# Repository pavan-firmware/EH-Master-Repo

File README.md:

# EH Home — Production Smart-Home Platform Monorepo

Welcome to the **EH Home** ecosystem repository. EH Home is an enterprise-grade, edge-autonomous, local-first smart-home platform supporting multi-gang smart switches (1X/2X/3X/4X), sockets, fan regulators, CCT/dimmable lighting, deterministic energy monitoring, on-chip FreeRTOS automation, and multi-protocol hardware abstraction (Wi-Fi, BLE, Thread, Matter).

---

## 1. Monorepo Architecture Overview

The workspace is organized as a unified monorepo engineered for strict contract safety, zero-downtime offline execution, and metadata-driven UI:

```
SMART_HOME_V1/
├── apps/
│   ├── api/                     # High-performance Fastify REST API & SSE Realtime Engine
│   └── desktop/                 # Tauri v2 + Rust + React Desktop Suite (Bench Provisioner, TSPL, Packing)
├── assets/                      # Brand, visual assets & product iconography
├── backend/                     # Node.js backend services, migrations, repositories & workers
│   ├── migrations/              # 37 symmetric UP/DOWN PostgreSQL migrations & seed data
│   ├── src/                     # Repositories, domain services, and REST/SSE API routers
│   └── tests/                   # Monorepo database integration, hardening & lifecycle test suites
├── docs/                        # Complete technical architecture, ADRs, runbooks & phase reports
│   ├── adr/                     # Architectural Decision Records (ADR-000 through ADR-004)
│   ├── architecture/            # Architecture specifications, Parts 00–17 & business guides
│   ├── contracts/               # Protocol contracts & deterministic energy specifications
│   ├── manufacturing/           # Factory bench provisioning & thermal label printing guides
│   └── reconciliation/          # Technical reconciliation audits & feature completion registers
├── firmware/                    # Production ESP32 embedded firmware
│   ├── platforms/esp32/         # FreeRTOS firmware (Edge Routine Engine, UDP Discovery, mTLS MQTT, OTA)
│   └── legacy-v1/               # Preserved legacy node/hub reference implementation
├── packages/
│   ├── contracts/               # Canonical Draft-07 JSON Schemas, TypeScript contracts & validators
│   └── db-schema/               # Drizzle ORM relational models & database definitions
├── product-definitions/         # Metadata-driven product catalog definitions (SKUs & hardware profiles)
├── smart_home_application_v1/   # Production Flutter mobile application (iOS, Android, Web)
│   ├── lib/                     # Stale-while-revalidate UI, capability engine, theme tokens, controllers
│   └── test/                    # Full unit, widget, lifecycle & capability regression test suites
├── tools/
│   ├── database/                # Backup, restore & replication utilities
│   ├── device-simulator/        # Contract-compliant device hardware simulator
│   ├── hardware-test-harness/   # Python hardware loopback and ESP32 lifecycle runner
│   └── manufacturing/           # Factory flasher, PKI manager & TSPL label generators
├── scripts/
│   └── validate-repo.js         # Master CI pre-push validation suite (80 comprehensive test suites)
├── .env.example                 # Local development configuration template
└── docker-compose.yml           # Local infrastructure stack (PostgreSQL, Redis, EMQX 5.8.0, MinIO)
```

---

## 2. Platform Architecture Phases (Phases 1 — 50)

| Phase Range | Subsystems Covered | Key Capabilities Implemented | Status |
|:---|:---|:---|:---:|
| **Phases 1–4** | Contracts, Persistence, Catalog & Domain | 19 canonical Draft-07 JSON schemas, PostgreSQL persistence, catalog discovery, home/floor/room/device domain entities. | ✅ Complete |
| **Phases 5–7** | Onboarding, Transports & Realtime | EH-PROV/1 BLE commissioning (AES-256-GCM, HKDF), EMQX 5.8.0 mTLS transport with per-device ACLs, RS256 JWT auth, realtime SSE event bus. | ✅ Complete |
| **Phases 8–11** | PKI, Automations & Fleet Reliability | Manufacturing root PKI, signed dual-slot OTA rollback, FreeRTOS edge routine engine, hardware watchdog & auto-healing. | ✅ Complete |
| **Phases 12–18** | Security, Fleet Rollout & Cloud Sync | Multi-tenant RBAC, remote backup storage, staggered OTA fleet deployments, disaster recovery snapshotting. | ✅ Complete |
| **Phases 19–25** | Energy, Tariffs & Decision Intelligence | Fixed-point energy telemetry (`BL0942`), ToU dynamic tariffs, energy optimization engine, occupancy presence inference. | ✅ Complete |
| **Phases 26–30** | Edge Control, Matter & User Alerts | Multi-protocol connectivity (Wi-Fi/BLE/Thread/Matter), local-first LAN UDP control (`<15ms`), smart notification de-duplication. | ✅ Complete |
| **Phases 31–36** | Security Hardening & Runtime Auth | Device trust center, cryptographic attestation, role-gated admin console, hardcoded breaker elimination, Flutter lifecycle convergence. | ✅ Complete |
| **Phases 37–46** | Database Scale, Manufacturing & Acceptance | 37 symmetric database migrations, MinIO S3 remote storage, bench flasher, automated thermal label printing, dual-scan packing station. | ✅ Complete |
| **Phases 47–48** | ESP32 Hardware Integration & RBAC | Physical ESP32 target verification, non-EM/EM switch variants, home ownership & membership RBAC (`OWNER`, `ADMIN`, `MEMBER`, `GUEST`). | ✅ Complete |
| **Phase 49** | Edge Routine Engine & Zero-Touch LAN | FreeRTOS on-chip timer routine engine, zero-touch UDP LAN switchover, dual-scan factory packing station, Windows PDF printing subsystem. | ✅ Complete |
| **Phase 50** | Resilience, Dark Theme & Master Flows | Offline stale-while-revalidate, dark-theme contrast tokens, routine notification filtering, truthful MQTT standby reporting, home owner admin access control. | ✅ Complete |

---

## 3. Core Architectural Principles

1. **Hardware is the Authority:** Physical switch toggles execute immediately at the hardware relay. Backend derives `actualState` from `reportedState`; conflicting in-flight cloud commands converge to `OVERRIDDEN`.
2. **Local-First & Edge-Autonomous:** Smart switches and sockets store routines in on-chip non-volatile storage (NVS). Routines execute via FreeRTOS hardware timers even if Wi-Fi or cloud connections are down.
3. **Zero-Touch LAN Control:** When the mobile app is on the local Wi-Fi network, commands travel directly over private LAN HTTP/UDP with `<15ms` latency. When outside, the app automatically transitions to TLS MQTT via the cloud backend.
4. **Role-Based Home Access Control (RBAC):**
   - **`OWNER`**: Full administrative authority over home, disaster recovery snapshots, device trust certificates, members, and billing.
   - **`ADMIN`**: Household management, rooms, device pairing, and routine scheduling.
   - **`MEMBER` / `GUEST`**: Day-to-day actuator controls and scene triggering with strict exclusion from system-level administrative pages.
5. **Deterministic Energy Telemetry:** All electrical measurements are fixed-point unsigned integers on wire (`v_mv`, `i_ma`, `p_mw`, `e_tot_wh`, `pf_x1000`) ensuring exact financial and consumption precision.
6. **Stale-While-Revalidate UX:** Settings, home details, dashboards, and routines display instantly from persistent local storage during offline cold starts or screenshot events, refreshing quietly in the background without blanking screens.

---

## 4. Local Development & Verification

### Prerequisites
- **Node.js**: `v20.x` or later (pnpm recommended)
- **Flutter SDK**: `3.12.x` or later (Dart 3.x)
- **Docker & Docker Compose** (for PostgreSQL, Redis, EMQX 5.8.0, MinIO)
- **Rust Toolchain**: `1.75+` (for Desktop Tauri suite)

### Quick Start
1. Copy the environment configuration:
   ```bash
   cp .env.example .env
   ```
2. Start local infrastructure services:
   ```bash
   docker compose up -d
   ```
3. Run the full pre-push validation suite (all 80 suites):
   ```bash
   node scripts/validate-repo.js
   ```
4. Run Flutter mobile application analyzer and tests:
   ```bash
   cd smart_home_application_v1
   flutter analyze
   flutter test
   ```

---

## 5. Master Validation Suite Overview

The monorepo includes an automated pre-push gate (`scripts/validate-repo.js`) executing **80 comprehensive test suites** covering all platform layers:

```
===============================================================
       EH HOME MONOREPO — PRE-PUSH FULL VALIDATION SUITE       
===============================================================
  [PASS]  1. Canonical Contract Hardening Tests
  [PASS]  2. Product Catalog Definition Validation
  [PASS]  3. Device Simulator Contract Compliance
  [PASS]  4. SQL Migration Lifecycle & Capability Sync (37 Migrations)
  [PASS]  5. Backend DB & Repository Integration Tests
  [PASS]  6. Backend Hardening Test Suite (Auth, State, Idempotency)
  [PASS]  7. Product Catalog Service & API Router Tests
  [PASS]  8. Phase 4 Backend Domain Model & Service Tests
  [PASS]  9. Phase 5 Backend Secure Onboarding & Claiming Tests
  [PASS] 10. Phase 6 MQTT Transport Unit/Mock Tests
  [PASS] 11. Phase 6 Low-Level MQTT Protocol Harness Tests
  [PASS] 12. Phase 6 Real EMQX 5.8.0 Integration Tests
  [PASS] 13. Phase 7A Backend Auth & Authorization Tests
  [PASS] 14. Phase 7B Realtime SSE & Worker Integration Tests
  [PASS] 15. Flutter Analyzer (smart_home_application_v1)
  [PASS] 16. Flutter Test Suite (smart_home_application_v1)
  ...
  [PASS] 72. Part 15 Desktop E2E & Cross-Layer Integration Tests
  [PASS] 73. Part 16 Storage Contracts Hardening
  [PASS] 74. Part 16 S3-Compatible Storage Provider Tests
  [PASS] 75. Part 16 Database Backup, Restore & Recovery Tests
  [PASS] 76. Part 16 Storage & Backup HTTP API Route Tests
===============================================================
  80 SUITES ATTEMPTED: 80 PASSED, 0 SKIPPED, 0 FAILED.
  ALL ATTEMPTED TEST SUITES COMPLETED WITHOUT FAILURE.
===============================================================
```

---

## 6. Security, Governance & Compliance

- **Zero Committed Secrets:** All certificates (`.pem`, `.crt`), keys (`.key`), and tokens are injected via environment variables or generated ephemerally during manufacturing bench flows.
- **Strict Lint & Contract Guard:** Any modification to schemas in `packages/contracts/` must pass Draft-07 validation and maintain bidirectional compatibility across mobile, backend, and firmware.
- **Git Housekeeping:** Test assets and scratch images (`prompt_images/`) are explicitly excluded from repository history via `.gitignore`.

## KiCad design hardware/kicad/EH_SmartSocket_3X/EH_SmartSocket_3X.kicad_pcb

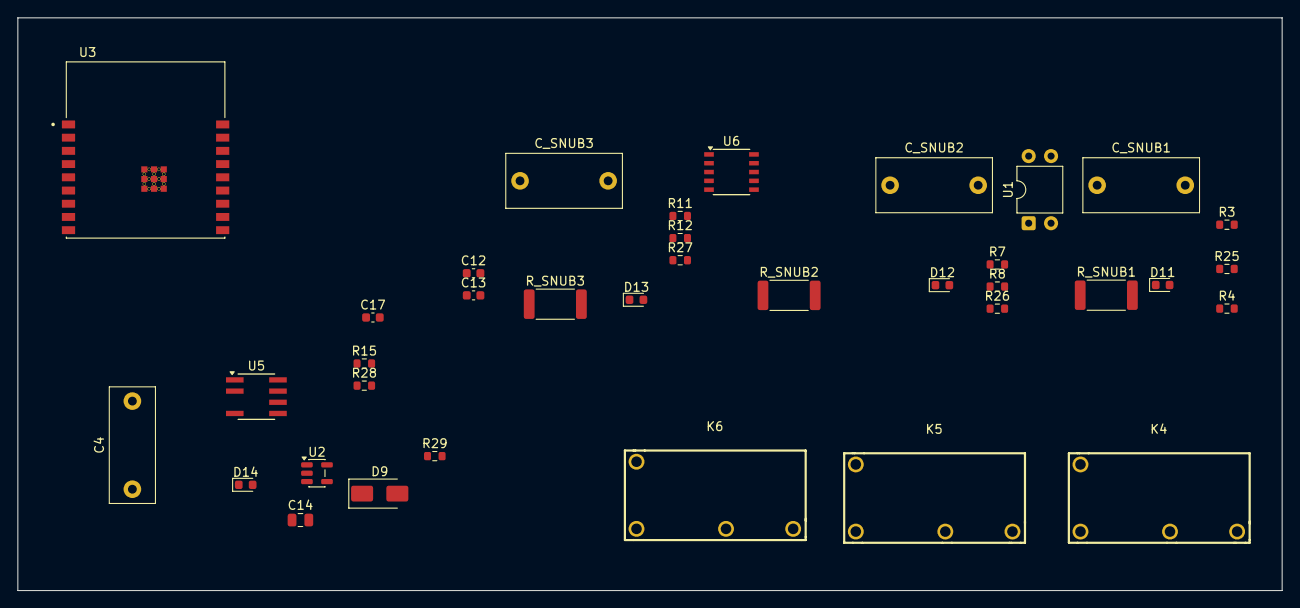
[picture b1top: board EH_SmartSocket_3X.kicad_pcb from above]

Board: 2 copper layers, 143.5 x 65.0 mm, 36 parts (0 on the bottom side), 31 nets, no tracks yet.

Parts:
C4: 0.1uF 275VAC X2; C_Rect_L13.0mm_W5.0mm_P10.00mm_FKS3_FKP3_MKS4
C12: 100nF; C_0603_1608Metric
C13: 1uF|16v; C_0603_1608Metric
C14: 10uF; C_0805_2012Metric
C17: 0.1uF; C_0603_1608Metric
C_SNUB1, C_SNUB2, C_SNUB3: 100nF|630V; C_Rect_L13.0mm_W6.0mm_P10.00mm_FKS3_FKP3_MKS4
D9: STTH1R06U; D_SMA
D11, D12, D13: LED_RL; LED_0603_1608Metric
D14: LED_GREEN; LED_0603_1608Metric
K4, K5, K6: HF33F/005-HS3; RELAYS-TH_HF33F-XX-HS1-XXX
R3, R7, R11, R25, R26, R27: 1K; R_0603_1608Metric
R4, R8, R12, R15, R29: 10K; R_0603_1608Metric
R28: 1.5K; R_0603_1608Metric
R_SNUB1, R_SNUB2, R_SNUB3: 100; R_2512_6332Metric
U1: PC817; DIP-4_W7.62mm
U2: AP2112K-3.3; SOT-23-5
U3: ESP32-C3-WROOM-02-N4; MODULE_ESP32-C3-WROOM-02-H4
U5: LNK3206D; PowerIntegrations_SO-8C
U6: SSOP-10_3.9x4.9mm_P1.00mm

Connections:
+3V3: C14.2, C17.1, R15.2, R28.1, R29.1, U2.5 (VOUT), U3.1 (3V3), U6.1 (VDD)
+5V: K4.1, K5.1, K6.1, R25.1, R26.1, R27.1, U1.1, U2.1 (VIN), U2.3 (EN)
/BL_RX: U3.6 (IO7), U6.10 (TX/SDO)
/BOOT_BTN: C12.2, R15.1, U3.8 (IO9)
/EN: C13.1, R29.2, U3.2 (EN)
/LKN_FB: U1.3, U5.2 (FB)
/LNK_BP: U1.4, U5.1 (BP/M)
/RLY_CH1: R3.1, U3.13 (IO18)
/RLY_CH2: R7.1, U3.14 (IO19)
/RLY_CH3: R11.1, U3.10 (IO10)
GND: C12.1, C13.2, C14.1, C17.2, D9.2 (A), D14.1 (K), R4.1, R8.1, R12.1, U2.2 (GND), U3.9 (GND), U3.19 (GND), U3.20 (GND), U3.21 (GND), U3.22 (GND), U3.23 (GND), U3.24 (GND), U3.25 (GND), U3.26 (GND), U3.27 (GND), U3.28 (GND), U3.29 (GND), U3.30 (GND), U3.31 (GND), U3.32 (GND), U3.33 (GND), U3.34 (GND), U3.35 (GND), U3.36 (GND), U3.37 (GND), U3.38 (GND), U3.39 (GND), U6.5 (GND), U6.7 (SEL), U6.8 (SCLK_BPS)
unnamed: C_SNUB1.1, R_SNUB1.2
unnamed: C_SNUB1.2, K4.3
unnamed: C_SNUB2.1, R_SNUB2.2
unnamed: C_SNUB2.2, K5.3
unnamed: C_SNUB3.1, R_SNUB3.2
unnamed: C_SNUB3.2, K6.3
unnamed: D9.1 (K), U5.5 (S), U5.6 (S), U5.7 (S), U5.8 (S)
unnamed: D11.2 (A), R25.2
unnamed: D11.1 (K), K4.6
unnamed: D12.2 (A), R26.2
unnamed: D12.1 (K), K5.6
unnamed: D13.2 (A), R27.2
unnamed: D13.1 (K), K6.6
unnamed: D14.2 (A), R28.2
unnamed: K4.2, R_SNUB1.1
unnamed: K5.2, R_SNUB2.1
unnamed: K6.2, R_SNUB3.1
unnamed: R3.2, R4.2
unnamed: R7.2, R8.2
unnamed: R11.2, R12.2

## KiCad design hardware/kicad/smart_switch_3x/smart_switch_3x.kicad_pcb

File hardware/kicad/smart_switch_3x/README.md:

# EH Home — KiCad 7 / 8 Production Hardware Project

This directory contains the **KiCad Schematic and PCB Design Project** for the **EH Smart Switch (3X / 4X Channel with BL0942 Metering)**.

---

## 1. Project Files

- **`smart_switch_3x.kicad_pro`**: KiCad Project File.
- **`smart_switch_3x.kicad_sch`**: KiCad Schematic Source.
- **`netlist_smart_switch_3x.net`**: Universal Netlist (can be imported into KiCad, EasyEDA, Altium, or OrCAD).

---

## 2. Universal Schematic Netlist & Pin Connections

Below is the complete machine-readable netlist and pin-to-pin wiring map:

### **Subsystem 1: Mains AC Input & Surge Protection**
| Component | Designator | Pin 1 | Pin 2 | Pin 3 / 4 / 5 | Notes |
| :--- | :--- | :--- | :--- | :--- | :--- |
| Screw Terminal (AC IN) | J1 | `MAINS_LIVE` | `MAINS_NEUTRAL` | `EARTH_GND` | 5.08mm pitch, 16A rated |
| Fuse 2A 250V | F1 | `MAINS_LIVE` | `FUSE_OUT` | — | Micro TR5 / Radial |
| Varistor (MOV) 14D561K | MOV1 | `FUSE_OUT` | `MAINS_NEUTRAL` | — | Clamps surges $\ge 350\text{VAC}$ / 560V |
| NTC Thermistor 10D-9 | NTC1 | `FUSE_OUT` | `AC_L_FILTERED` | — | Limits inrush current |
| Safety Cap 0.1µF 275VAC | CX1 | `AC_L_FILTERED` | `MAINS_NEUTRAL` | — | Class-X2 EMI Suppression |
| Isolated SMPS (HLK-PM01) | U2 | Pin 1: `AC_L_FILTERED` | Pin 2: `MAINS_NEUTRAL` | Pin 3: `+5V`, Pin 4: `GND` | 3kV Isolation AC $\to$ 5V DC |

---

### **Subsystem 2: Low-Voltage Power Regulation (5V $\to$ 3.3V)**
| Component | Designator | Pin 1 | Pin 2 | Pin 3 | Pin 4 | Pin 5 |
| :--- | :--- | :--- | :--- | :--- | :--- | :--- |
| LDO Regulator (AP2112K-3.3) | U3 | `+5V` (VIN) | `GND` | `+5V` (EN) | `NC` | `+3V3` (VOUT) |
| Bulk Filter Capacitor | C1 | `+5V` | `GND` | — | — | 470µF 16V Low-ESR |
| LDO Output Capacitor | C2 | `+3V3` | `GND` | — | — | 100µF 10V Tantalum/Alum |
| Decoupling Capacitors | C3, C4 | `+3V3` | `GND` | — | — | 0.1µF 50V X7R (0603) |

---

### **Subsystem 3: Microcontroller (ESP32-C6-WROOM-1-N4)**
| Pin Name | ESP32-C6 Pin | Connected Net | Description / Function |
| :--- | :--- | :--- | :--- |
| `3V3` | Pin 1, 2 | `+3V3` | Main 3.3V Power Rail |
| `GND` | Pin 3, 14, 29 | `GND` | System Digital Ground |
| `EN` / `CHIP_PU` | Pin 4 | `MCU_EN` | 10kΩ pull-up to 3.3V + 1µF cap to GND |
| `GPIO 4` | Pin 5 | `SW_IN_1` | Channel 1 Wall Switch Input (RC Filtered) |
| `GPIO 5` | Pin 6 | `SW_IN_2` | Channel 2 Wall Switch Input (RC Filtered) |
| `GPIO 6` | Pin 7 | `SW_IN_3` | Channel 3 Wall Switch Input (RC Filtered) |
| `GPIO 7` | Pin 8 | `BL0942_TX_OUT` | BL0942 UART1 Data In (4800 baud) |
| `GPIO 8` | Pin 9 | `STATUS_LED_DRIVE` | 1kΩ Resistor $\to$ Blue Status LED $\to$ GND |
| `GPIO 9` | Pin 10 | `BOOT_SW` | Tactile Button to GND (10s Hold = Reset) |
| `GPIO 16` | Pin 17 | `FACTORY_TX` | Factory Programming UART0 TX (Pogo Pad 3) |
| `GPIO 17` | Pin 18 | `FACTORY_RX` | Factory Programming UART0 RX (Pogo Pad 4) |
| `GPIO 18` | Pin 19 | `RELAY_DRV_1` | 1kΩ Resistor $\to$ Q1 MOSFET Gate |
| `GPIO 19` | Pin 20 | `RELAY_DRV_2` | 1kΩ Resistor $\to$ Q2 MOSFET Gate |
| `GPIO 20` | Pin 21 | `RELAY_DRV_3` | 1kΩ Resistor $\to$ Q3 MOSFET Gate |

---

### **Subsystem 4: Relay Actuation & Snubber (Channels 1, 2, 3)**
| Component | Channel 1 | Channel 2 | Channel 3 | Connections |
| :--- | :--- | :--- | :--- | :--- |
| **N-MOSFET Driver** | Q1 (AO3400A) | Q2 (AO3400A) | Q3 (AO3400A) | Gate: 1kΩ from GPIO, 10kΩ to GND; Source: GND; Drain: Relay Coil Pin 2 |
| **Flyback Diode** | D1 (SS14) | D2 (SS14) | D3 (SS14) | Cathode: `+5V`; Anode: MOSFET Drain |
| **10A Power Relay** | K1 (HF32F-G) | K2 (HF32F-G) | K3 (HF32F-G) | Coil 1: `+5V`; Coil 2: MOSFET Drain; COM: `MAINS_LIVE`; NO: `LOAD_OUT_CHx` |
| **Snubber Resistor** | RS1 (100Ω 1W) | RS2 (100Ω 1W) | RS3 (100Ω 1W) | In series with Snubber Cap across COM & NO |
| **Snubber Capacitor**| CS1 (100nF 630V)| CS2 (100nF 630V)| CS3 (100nF 630V)| In series with Snubber Resistor across COM & NO |

---

### **Subsystem 5: Wall Switch Noise & ESD Filter (Channels 1, 2, 3)**
| Component | Channel 1 | Channel 2 | Channel 3 | Connections |
| :--- | :--- | :--- | :--- | :--- |
| **Pull-Up Resistor** | R_PU1 (10kΩ) | R_PU2 (10kΩ) | R_PU3 (10kΩ) | Connected between `+3V3` and Switch Terminal Pin |
| **Series Resistor** | R_S1 (1kΩ) | R_S2 (1kΩ) | R_S3 (1kΩ) | In series between Switch Terminal and ESP32 GPIO |
| **TVS Clamp Diode** | D_TVS1 (ESD5Z3.3)| D_TVS2 (ESD5Z3.3)| D_TVS3 (ESD5Z3.3)| Connected between GPIO Line and `GND` |
| **Filter Capacitor** | C_SW1 (100nF) | C_SW2 (100nF) | C_SW3 (100nF) | Connected between GPIO Line and `GND` |

---

### **Subsystem 6: BL0942 Energy Metering (SOP-14)**
| BL0942 Pin | Pin Name | Connected To | Circuit Components |
| :--- | :--- | :--- | :--- |
| Pin 1 | `VDD` | `+3V3` | 0.1µF + 10µF bypass capacitors to GND |
| Pin 2 | `IP` | Positive Current Sense | 33Ω series resistor $\to$ Shunt Resistor (High Side) + 10nF to GND |
| Pin 3 | `IN` | Negative Current Sense | 33Ω series resistor $\to$ Shunt Resistor (Low Side) + 10nF to GND |
| Pin 4 | `VP` | Voltage Sense | 33Ω series resistor $\to$ (4x 240kΩ Divider tap) + 10nF to GND |
| Pin 5 | `GND` | `GND` | Direct to digital ground polygon |
| Pin 11 | `TX` | `GPIO 7` (ESP32-C6) | Direct UART connection at 4800 baud |

---

## 3. How to Open & Export in KiCad 7 / 8

1. Launch **KiCad 7** or **KiCad 8**.
2. Click **File $\longrightarrow$ Open Project** and select `smart_switch_3x.kicad_pro`.
3. Open the Schematic Editor to view and edit symbols, run **Electrical Rules Check (ERC)**.
4. Press `[F8]` (**Update PCB from Schematic**) to auto-place footprints and begin routing with 2oz copper and isolation slots.

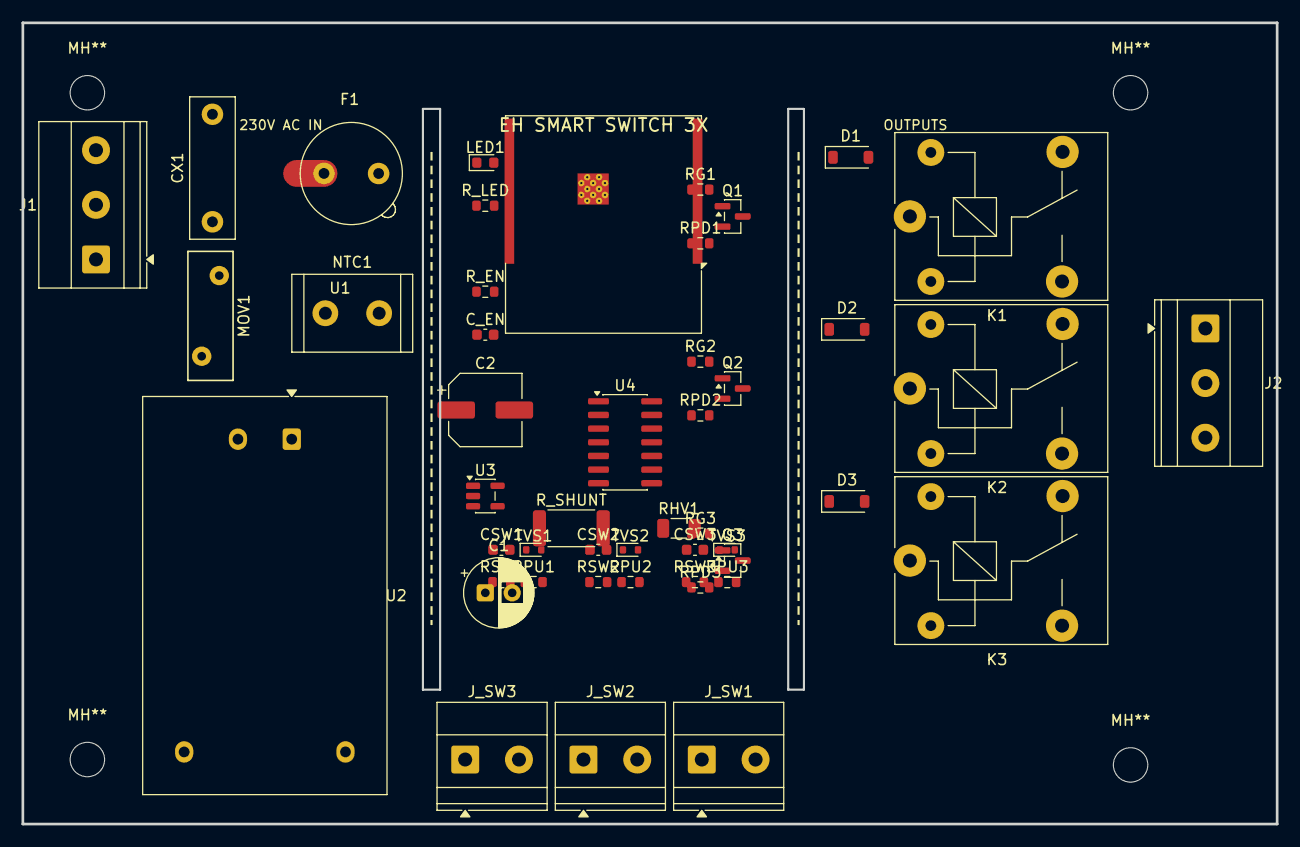
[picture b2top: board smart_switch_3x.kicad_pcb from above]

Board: 2 copper layers, 116.6 x 74.5 mm, 52 parts (0 on the bottom side), 18 nets.

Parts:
C1: 470uF_16V; CP_Radial_D6.3mm_P2.50mm
C2: 100uF_10V; CP_Elec_6.3x5.8
CSW1, CSW2, CSW3: 100nF; C_0603_1608Metric
CX1: 0.1uF_275V; C_Rect_L13.0mm_W4.0mm_P10.00mm_FKS3_FKP3_MKS4
C_EN: 1uF; C_0603_1608Metric
D1, D2, D3: SS14; D_SOD-123
F1: 2A_250V; Fuseholder_TR5_Littelfuse_No560_No460
J1: MAINS_IN; TerminalBlock_Phoenix_MKDS-1,5-3-5.08_1x03_P5.08mm_Horizont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
J2: LOAD_OUTPUTS; TerminalBlock_Phoenix_MKDS-1,5-3-5.08_1x03_P5.08mm_Horizont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
J_SW1: WALL_SW_1; TerminalBlock_Phoenix_MKDS-1,5-2_1x02_P5.00mm_Horizontal
J_SW2: WALL_SW_2; TerminalBlock_Phoenix_MKDS-1,5-2_1x02_P5.00mm_Horizontal
J_SW3: WALL_SW_3; TerminalBlock_Phoenix_MKDS-1,5-2_1x02_P5.00mm_Horizontal
K1, K2, K3: HF32F-G_10A; Relay_SPDT_SANYOU_SRD_Series_Form_C
LED1: BLUE_0603; LED_0603_1608Metric
MH**: M3; MountingHole_3.2mm_M3
MH**#2, MH**#3, MH**#4: M3; MountingHole_3.2mm_M3
MOV1: 14D561K; RV_Disc_D12mm_W4.2mm_P7.5mm
NTC1: 10D-9; R_Radial_Power_L11.0mm_W7.0mm_P5.00mm
Q1, Q2, Q3: AO3400A; SOT-23
RG1, RG2, RG3: 1k; R_0603_1608Metric
RHV1: 960k_HV; R_1206_3216Metric
RPD1, RPD2, RPD3: 10k; R_0603_1608Metric
RPU1, RPU2, RPU3: 10k; R_0603_1608Metric
RSW1, RSW2, RSW3: 1k; R_0603_1608Metric
R_EN: 10k; R_0603_1608Metric
R_LED: 1k; R_0603_1608Metric
R_SHUNT: 1mOhm_2W; R_2512_6332Metric
TVS1, TVS2, TVS3: ESD5Z3.3; D_SOD-523
U1: ESP32-C6-WROOM-1; ESP32-C3-WROOM-02
U2: HLK-PM01_5V; Converter_ACDC_Hi-Link_HLK-PMxx
U3: AP2112K-3.3; SOT-23-5
U4: BL0942_SOP14; SOIC-14_3.9x8.7mm_P1.27mm

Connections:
+3V3: C2.1, C_EN.1, RPU1.1, RPU2.1, RPU3.1, R_EN.1, R_EN.2, U1.1, U1.2, U3.5, U4.1
+5V: C1.1, D1.1, D2.1, D3.1, K1.1, K2.1, K3.1, U2.3, U3.1, U3.3
AC_L_FILTERED: CX1.1, F1.2, MOV1.1, NTC1.1, NTC1.2, U2.1
BL0942_TX: U1.7, U4.11
GND: C1.2, C2.2, CSW1.2, CSW2.2, CSW3.2, C_EN.2, J1.3, J_SW1.2, J_SW2.2, J_SW3.2, LED1.2, Q1.2, Q2.2, Q3.2, RHV1.2, RPD1.2, RPD2.2, RPD3.2, TVS1.2, TVS2.2, TVS3.2, U1.3, U2.4, U3.2, U4.5
LOAD_CH1: J2.1, K1.3
LOAD_CH2: J2.2, K2.3
LOAD_CH3: J2.3, K3.3
MAINS_LIVE: F1.1, J1.1, K1.5, K2.5, K3.5, RHV1.1, U4.4
MAINS_NEUTRAL: CX1.2, J1.2, MOV1.2, R_SHUNT.1, U2.2, U4.2
NEUTRAL_LOAD: R_SHUNT.2, U4.3
RELAY_DRV_1: D1.2, K1.2, Q1.1, Q1.3, RG1.1, RG1.2, RPD1.1, U1.18
RELAY_DRV_2: D2.2, K2.2, Q2.1, Q2.3, RG2.1, RG2.2, RPD2.1, U1.19
RELAY_DRV_3: D3.2, K3.2, Q3.1, Q3.3, RG3.1, RG3.2, RPD3.1
STATUS_LED: LED1.1, R_LED.1, R_LED.2, U1.8
SW_IN_1: CSW1.1, J_SW1.1, RPU1.2, RSW1.1, RSW1.2, TVS1.1, U1.4
SW_IN_2: CSW2.1, J_SW2.1, RPU2.2, RSW2.1, RSW2.2, TVS2.1, U1.5
SW_IN_3: CSW3.1, J_SW3.1, RPU3.2, RSW3.1, RSW3.2, TVS3.1, U1.6

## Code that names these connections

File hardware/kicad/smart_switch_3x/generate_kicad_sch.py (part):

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
    # Block 1: Mains Protection
    add_sym("Connector:Conn_01x03", 35.0, 55.0, "J1", "MAINS_IN", "TerminalBlock_Phoenix:TerminalBlock_Phoenix_MKDS-1,5-3-5.08_1x03_P5.08mm_Horizontal")
    add_label("MAINS_LIVE", 40.08, 52.46)
    add_label("MAINS_NEUTRAL", 40.08, 55.0)
    add_label("EARTH_GND", 40.08, 57.54)

    add_sym("Device:Fuse", 60.0, 52.46, "F1", "2A_250V", "smart_switch_3x:Fuse_TR5", 0)
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    add_wire(115.0, 58.81, 115.0, 60.0)
    add_wire(80.0, 60.0, 115.0, 60.0)

    add_label("AC_L_FILTERED", 125.0, 52.46)
    add_wire(115.0, 52.46, 125.0, 52.46)
    add_label("AC_N_FILTERED", 125.0, 60.0)
    add_wire(115.0, 60.0, 125.0, 60.0)

    # Block 2: Power Supply
    add_sym("Power_Supply:HLK-PM01", 185.0, 55.0, "U2", "HLK-PM01_5V", "smart_switch_3x:HLK-PM01")
    add_label("AC_L_FILTERED", 172.3, 49.92, 180)
    add_label("AC_N_FILTERED", 172.3, 60.08, 180)
    add_pwr("power:+5V", 205.0, 49.92, "+5V")
    add_wire(197.7, 49.92, 205.0, 49.92)
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    add_wire(38.0, 138.81, 38.0, 142.0)

    # Switch Inputs & Telemetry to MCU
    add_label("SW_IN_1", 49.76, 129.92, 180)
    add_label("SW_IN_2", 49.76, 135.0, 180)
    add_label("SW_IN_3", 49.76, 140.08, 180)
    add_label("BL0942_TX_OUT", 49.76, 145.16, 180)
    add_label("STATUS_LED", 49.76, 150.24, 180)
    add_label("BOOT_BTN", 49.76, 155.32, 180)

    # Relay Outputs from MCU
    add_label("RELAY_DRV_1", 80.24, 124.84)
    add_label("RELAY_DRV_2", 80.24, 129.92)
    add_label("RELAY_DRV_3", 80.24, 135.0)
    add_label("FACTORY_TX0", 80.24, 145.16)
    add_label("FACTORY_RX0", 80.24, 150.24)

    # Status LED & Boot Switch Circuit
    add_sym("Device:R", 100.0, 150.24, "R_LED2", "1k", "Resistor_SMD:R_0603_1608Metric", 90)
    add_label("STATUS_LED", 93.0, 150.24, 180)
    add_wire(93.0, 150.24, 96.19, 150.24)
    add_sym("Device:LED", 112.0, 150.24, "LED1", "BLUE_0603", "LED_SMD:LED_0603_1608Metric", 0)
    add_wire(103.81, 150.24, 108.19, 150.24)
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        add_wire(222.62, y_pos+2.54, 255.0, y_pos+2.54)
        add_wire(255.0, y_pos-2.54, 255.0, y_pos+2.54)

        add_label("MAINS_LIVE", 222.62, y_pos-2.54)
        add_label(f"LOAD_CH{ch}", 222.62, y_pos+2.54)

    # Block 5: BL0942 Telemetry
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
    # Shunt & Voltage Dividers
    add_sym("Device:R", 30.0, 212.46, "R_SHUNT2", "1mOhm_2W_1%", "Resistor_SMD:R_2512_6332Metric", 0)
    add_label("MAINS_NEUTRAL", 30.0, 206.0, 90)
    add_wire(30.0, 206.0, 30.0, 208.65)
    add_label("NEUTRAL_LOAD", 30.0, 220.0, 270)
    add_wire(30.0, 216.27, 30.0, 220.0)
    add_wire(30.0, 208.65, 52.3, 212.46)
    add_wire(30.0, 216.27, 52.3, 217.54)

    add_sym("Device:R", 38.0, 222.62, "RHV1", "960k_HV", "Resistor_SMD:R_1206_3216Metric", 90)
    add_label("MAINS_LIVE", 25.0, 222.62, 180)
    add_wire(25.0, 222.62, 34.19, 222.62)
    add_wire(41.81, 222.62, 52.3, 222.62)

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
